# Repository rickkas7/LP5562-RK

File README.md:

# LP5562-RK

*LP5562 I2C LED Driver for Particle devices*

There are several possibilities for indicator RGB LEDs:

- Direct connection to PWM outputs
- Serial LEDs like NeoPixels (WS2812)
- I2C LED drivers

Direct PWM is the least expensive, but when you are using RGB LEDs you'll quickly run out of available PWM channels. You're pretty much limited to one additional RGB LED on most devices.

NeoPixels are a great option as you can string together dozens of LEDs off a single GPIO. There are a few downsides:

- You need to have 3.6V or higher. You can't run them off 3.3V.
- The NeoPixel library runs for long periods of time with interrupts disabled for long strands, which may affect performance of other code.

The third option is to use an I2C LED driver. That's what this library is for. It allows the use of the TI LP5562 I2C LED driver from a Particle device. Why it this useful?

- It runs at 3.3V
- Uses cheap off-the-shelf RGB LEDs
- You can include up to 4 of them on the I2C bus
- It can drive LEDs up to 25.5 mA, great for large indicator LEDs
- It has a programmable constant current driver so you don't need current limiting resistors
- It's a programmable smart controller so many LED patterns can be made without intervention from the MCU

What's the downside? It does add a chip ($1.14 in single quantities). The biggest challenge is that it's only available in a DSBGA12 package. This is a really, really tiny 3x4 BGA (ball grid array) chip. 1.648 mm x 1.248 mm. It's barely larger than an 0805 resistor, but with 12 pins. It can only be reflowed; it's obviously not possible to solder with a soldering iron.

On the plus side, you can put one of these on your board and it takes up less space than 3x  0603 current limiting resistors.

While it's designed to drive an RGB LED plus one extra LED (white), it actually can drive any four independent LEDs. There are a couple benefits of using "indicator mode":

- You can drive 4x LEDs up to 25.5 mA
- Only uses I2C, no GPIO
- Full programmable to be on/dim/off, plus programmable patterns like blink or breathe

### The library

Using the LP5562-RK library is just a matter of adding the library to your project and initializing it:

```
#include "LP5562-RK.h"

LP5562 ledDriver;

void setup() {
	ledDriver.withLEDCurrent(5.0).begin();

	ledDriver.setBreathe(false, true, true, 20, 0, 255);
}

void loop() {
}
```

You normally allocate the object as a global object:

```
LP5562 ledDriver;
```

In setup(), initialize the object. There are some options that you configure fluent-style then call the begin() method:

```
ledDriver.withLEDCurrent(5.0).begin();
```

There are methods to set a constant color, blink, alternating blink, and breathe. This call does cyan breathing:

```
ledDriver.setBreathe(false, true, true, 20, 0, 255);
```

The options left to right are:

- red (disabled)
- green (enabled)
- blue (enabled) (green + blue = cyan)
- 20 the number of half milliseconds per step (10 milliseconds)
- 0 starting brightness 
- 255 ending brightness

[Full browsable API docs](https://rickkas7.github.io/LP5562-RK/index.html) are available. The calls are extensively documented in the .h file. There's also a copy of the HTML docs in the docs subdirectory.

The three example programs illustrate all of the features.

### I2C addressing

The LP5562 has two address select lines to allow you to connect four to a single I2C bus, using address 0x30 to 0x33.

Because of the closeness of the BGA balls if you use the external clock you'll probably be limited to using the single I2C address 0x30. The reason is that you'll probably need to route ground through pins B1 (AD1), B2 (AD0), to B3 (GND).

If you're not using an external clock and using the same power supply for VCC and VDD, then life is much easier, and all addresses are easily routed:

Address 0 (AD1 = 0, AD0 = 0, 0x30):

Address 1 (AD1 = 0, AD0 = 1, 0x31):

Address 2 (AD1 = 1, AD0 = 0, 0x32):

Address 3 (AD1 = 1, AD0 = 1, 0x33):

### RGB Demo Board

I made a simple demo board to test and illustrate the use of the chip. 

Here's the schematic.

And the board. It's an Adafruit Feather form-factor, intended to be used in a double or tripler with a Gen 3 Particle device (Argon, Boron, or Xenon). Male header pins go on the bottom side.

Close-up of the LED circuitry:

The eagle subdirectory contains the open source design:

- LedDriverTest1.sch (schematic)
- LedDriverTest1.brd (board layout)
- LedDriverTest1v1.zip (gerbers)
- LedDriverTest1.lbr (library with all of the components used on the board)

| Quantity | Item | Example | Price |
| --- | --- | --- | ---: |
| 1 | LP5562 | [LP5562TMX/NOPB ](https://www.digikey.com/product-detail/en/texas-instruments/LP5562TMX-NOPB/296-39061-1-ND/5142961) | $1.14 |
| 1 | RGB LED | [Cree CLMVC-FKA-CL1D1L71BB7C3C3](https://www.digikey.com/product-detail/en/cree-inc/CLMVC-FKA-CL1D1L71BB7C3C3/CLMVC-FKA-CL1D1L71BB7C3C3CT-ND/9094273 CLMVC-FKA-CL1D1L71BB7C3C3) | $0.19 |
| 1 | White LED | [Lite-On Inc. LTW-C191DS5](https://www.digikey.com/product-detail/en/lite-on-inc/LTW-C191DS5/160-2239-1-ND/7708913) | $0.55 |
| 2 | 10K Resistor 0603 | [Panasonic ERJ-PA3J103V](https://www.digikey.com/product-detail/en/panasonic-electronic-components/ERJ-PA3J103V/P10KBZCT-ND/5036237) | $0.10 | 
|   | Male header pins 0.1" | [Sullins PRPC040SAAN-RC](https://www.digikey.com/product-detail/en/PRPC040SAAN-RC/S1011EC-40-ND/2775214) |  |

### Indicator Demo Board

This demo board tests 4 discrete LEDs instead of using an RGB LED. I made it using T-1 (3mm) through hole LEDs because I had a kit of them so I could use 3 20mA LEDs and 1 10mA LEDs. 

Schematic:

Board:

The main difference between indicator mode and RGB mode is how the engines are set up. Because there are four LEDs and 3 engines, indicator mode sets up the three engines with common patterns:

- Blink
- Fast blink
- Breathe

Then you can assign any LED to be on, dim, off, or one of the three available patterns. This provides a lot of flexibility given the hardware limitations of the LP5562. Of course the full LP5562 programming API is available as well if you want to go crazy with the customization.

If you are using LEDs with different current requirements you can use the `withLEDCurrent()` overload with separate settings for red, green, blue, and white. 

```
ledDriver.withLEDCurrent(20.0, 20.0, 20.0, 10.0).begin();
```

To use indicator mode, use `setIndicatorMode()`.

```
ledDriver.setIndicatorMode();
```

To set an LED, use one of the setLedMapping methods:

```
ledDriver.setLedMappingR(LP5562::REG_LED_MAP_DIRECT, 0);
ledDriver.setLedMappingG(LP5562::REG_LED_MAP_ENGINE_1);
ledDriver.setLedMappingB(LP5562::REG_LED_MAP_ENGINE_2);
ledDriver.setLedMappingW(LP5562::REG_LED_MAP_ENGINE_3);
```

- `LP5562::REG_LED_MAP_DIRECT` sets a direct PWM value. 0 is off, 255 is full brightness, and values in between are dimmed.
- `LP5562::REG_LED_MAP_ENGINE_1` is a normal blink. 
- `LP5562::REG_LED_MAP_ENGINE_2` is a fast blink.
- `LP5562::REG_LED_MAP_ENGINE_3` is breathing.

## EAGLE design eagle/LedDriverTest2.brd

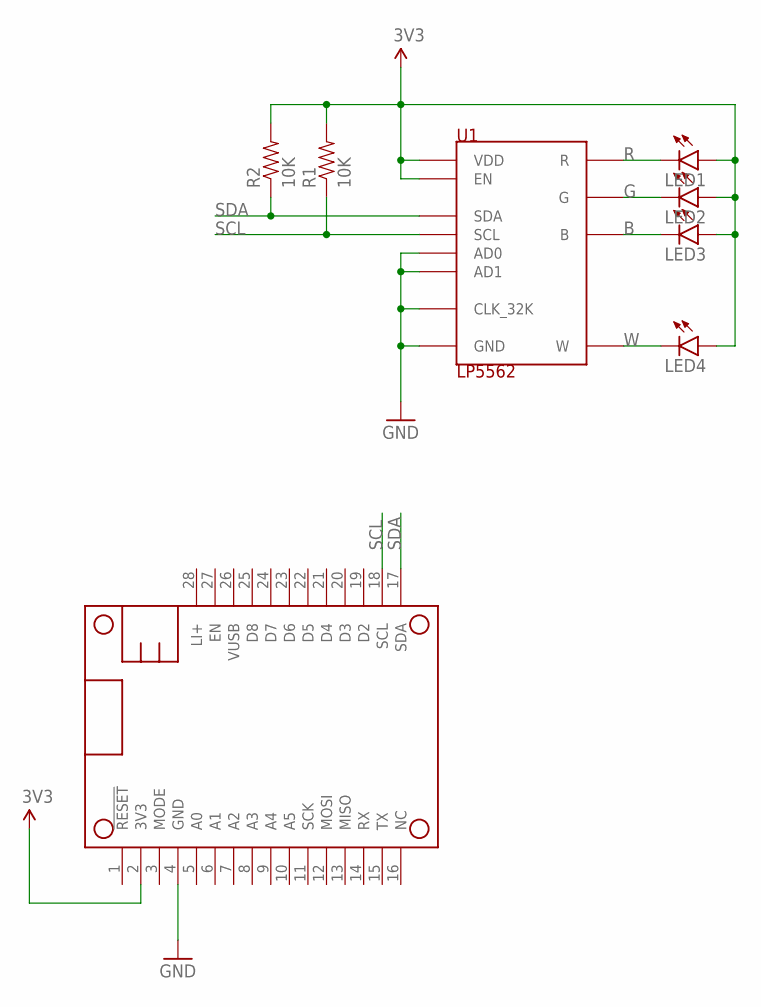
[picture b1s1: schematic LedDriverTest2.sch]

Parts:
LED1, LED2, LED3, LED4: LED3MM
MS1: FEATHERWING_NODIM
R1, R2: 10K; 0603-RES
U1: LP5562; DSBGA12-TI

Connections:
3V3: LED1.A, LED2.A, LED3.A, LED4.A, MS1.2 (3V3), R1.2, R2.2, U1.A2 (VDD), U1.C3 (EN)
B: LED3.K (C), U1.A4 (B)
G: LED2.K (C), U1.B4 (G)
GND: MS1.4 (GND), U1.A3 (CLK_32K), U1.B1 (AD1), U1.B2 (AD0), U1.B3 (GND)
R: LED1.K (C), U1.C4 (R)
SCL: MS1.18 (SCL), R1.1, U1.C2 (SCL)
SDA: MS1.17 (SDA), R2.1, U1.C1 (SDA)
W: LED4.K (C), U1.A1 (W)

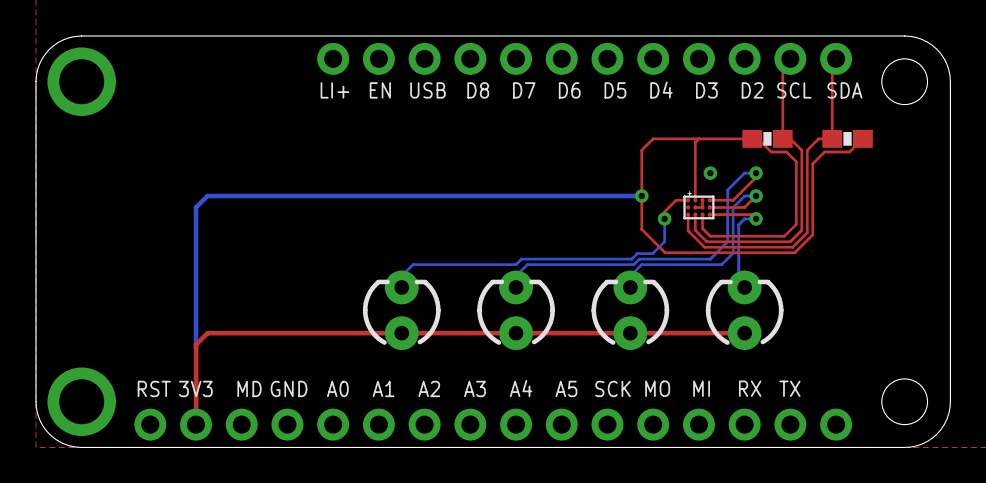
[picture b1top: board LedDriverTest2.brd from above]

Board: 2 copper layers, 50.8 x 22.9 mm, 8 parts (0 on the bottom side), 8 nets.

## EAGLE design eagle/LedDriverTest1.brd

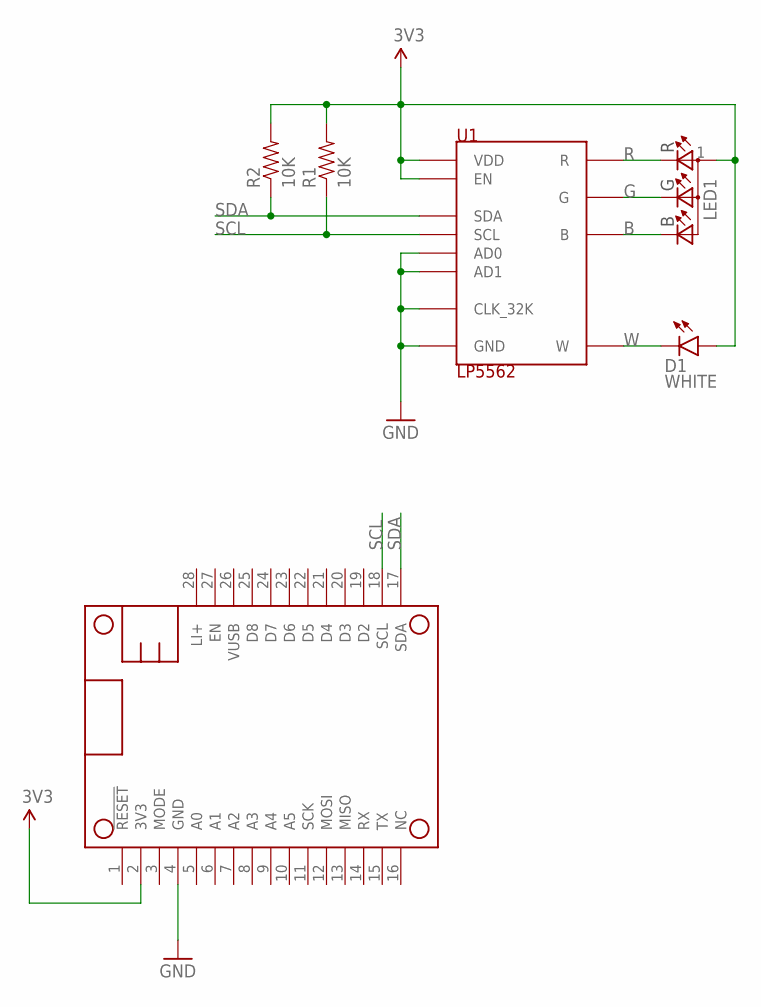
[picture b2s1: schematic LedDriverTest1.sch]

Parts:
D1: WHITE; LED-0603
LED1: RGB; LED-RGB-CREE-SMD
MS1: FEATHERWING_NODIM
R1, R2: 10K; 0603-RES
U1: LP5562; DSBGA12-TI

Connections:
3V3: D1.A, LED1.1 (A), MS1.2 (3V3), R1.2, R2.2, U1.A2 (VDD), U1.C3 (EN)
B: LED1.2 (B), U1.A4 (B)
G: LED1.3 (G), U1.B4 (G)
GND: MS1.4 (GND), U1.A3 (CLK_32K), U1.B1 (AD1), U1.B2 (AD0), U1.B3 (GND)
R: LED1.4 (R), U1.C4 (R)
SCL: MS1.18 (SCL), R1.1, U1.C2 (SCL)
SDA: MS1.17 (SDA), R2.1, U1.C1 (SDA)
W: D1.C, U1.A1 (W)

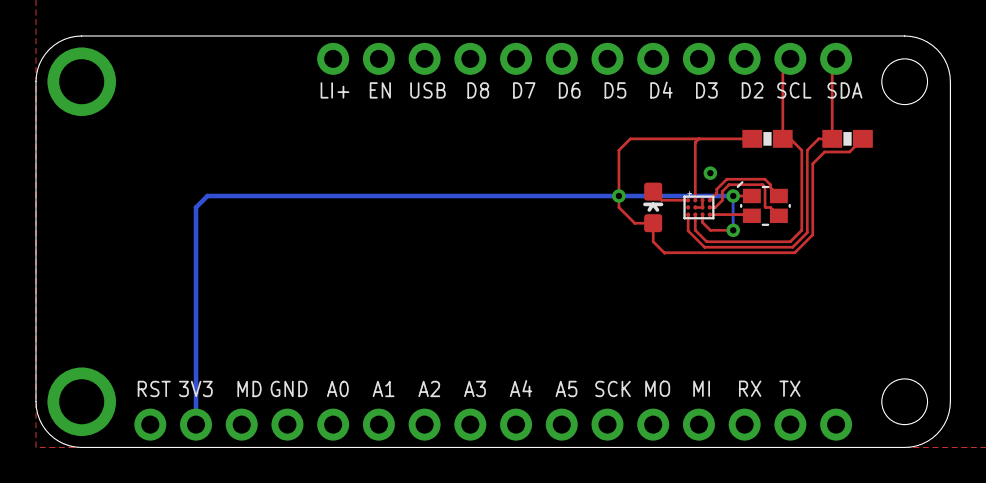
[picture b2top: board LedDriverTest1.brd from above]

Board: 2 copper layers, 50.8 x 22.9 mm, 6 parts (0 on the bottom side), 8 nets.

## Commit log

2019-07-28 Initial check-in
2019-08-14 Version 0.0.2
    - Added indicator mode

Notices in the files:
parts and their libraries:
SparkFun-LED: Licensing: Creative Commons ShareAlike 4.0 International - https://creativecommons.org/licenses/by-sa/4.0
